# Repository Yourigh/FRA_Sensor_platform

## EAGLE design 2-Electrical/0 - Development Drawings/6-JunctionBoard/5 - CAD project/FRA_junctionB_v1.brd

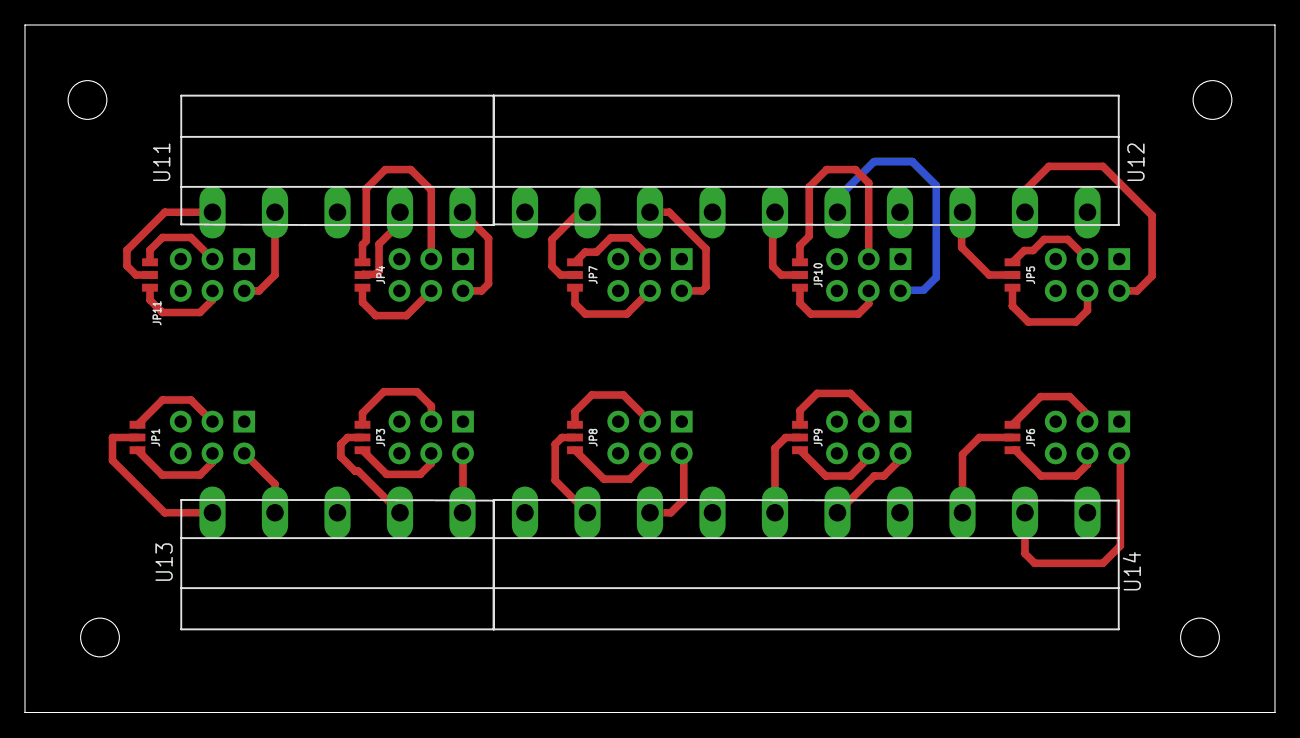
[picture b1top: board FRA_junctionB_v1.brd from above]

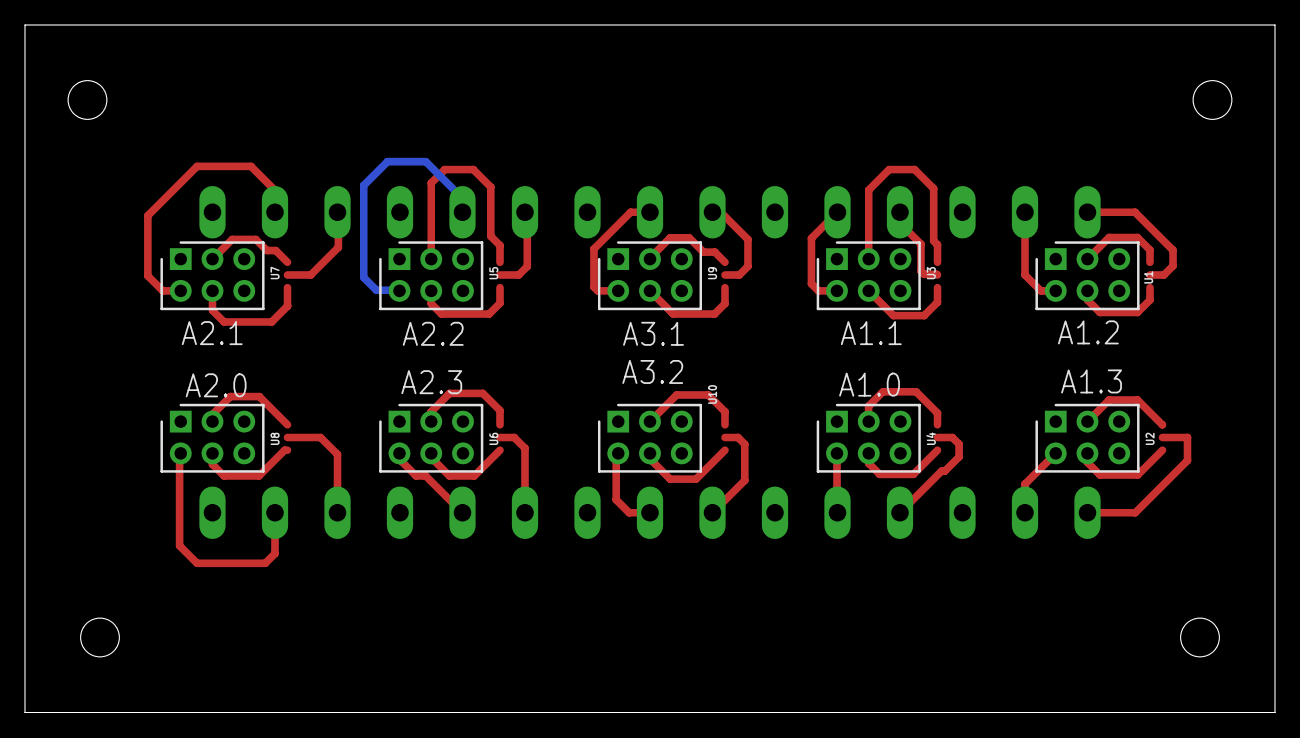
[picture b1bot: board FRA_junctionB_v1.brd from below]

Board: 2 copper layers, 100.0 x 55.0 mm, 24 parts (10 on the bottom side), 32 nets.

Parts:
JP1, JP3, JP4, JP5, JP6, JP7, JP8, JP9, JP10, JP11: JUMPER-SMT_3_NO_NO_SILK; SMT-JUMPER_3_0-NO_TRACE_NO-SILK
U1, U2, U3, U4, U5, U6, U7, U8, U9, U10: SSW-103-01-F-D; SHDR6W79P254_2X3_813X495X851P
U11, U13: TB003V-500-P05BE
U12, U14: TB003V-500-P10BE

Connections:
5V_CALM: JP1.1, JP3.1, JP4.1, JP5.1, JP6.1, JP7.1, JP8.1, JP9.1, JP10.1, JP11.1, U1.3, U2.3, U3.3, U4.3, U5.3, U6.3, U7.3, U8.3, U9.3, U10.3
ADC1_1: U1.2, U11.4
ADC1_2: U2.2, U13.2
ADC1_3: U3.2, U11.1
ADC1_4: U4.2, U13.5
ADC2_1: U5.2, U12.5
ADC2_2: U6.2, U14.6
ADC2_3: U7.2, U12.2
ADC2_4: U8.2, U14.9
ADC3_1: U9.2, U12.8
ADC3_2: U10.2, U14.3
AGND: U1.1, U2.1, U3.1, U4.1, U5.1, U6.1, U7.1, U8.1, U9.1, U10.1, U11.3, U12.1, U12.4, U12.7, U12.10, U13.3, U14.1, U14.4, U14.7, U14.10
unnamed: JP1.2, U13.1
unnamed: JP1.3, U2.4
unnamed: JP3.2, U13.4
unnamed: JP3.3, U4.4
unnamed: JP4.2, U11.2
unnamed: JP4.3, U3.4
unnamed: JP5.2, U12.3
unnamed: JP5.3, U7.4
unnamed: JP6.2, U14.8
unnamed: JP6.3, U8.4
unnamed: JP7.2, U12.9
unnamed: JP7.3, U9.4
unnamed: JP8.2, U14.2
unnamed: JP8.3, U10.4
unnamed: JP9.2, U14.5
unnamed: JP9.3, U6.4
unnamed: JP10.2, U12.6
unnamed: JP10.3, U5.4
unnamed: JP11.2, U11.5
unnamed: JP11.3, U1.4

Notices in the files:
parts and their libraries:
SparkFun-Jumpers: Licensing: Creative Commons ShareAlike 4.0 International - https://creativecommons.org/licenses/by-sa/4.0
